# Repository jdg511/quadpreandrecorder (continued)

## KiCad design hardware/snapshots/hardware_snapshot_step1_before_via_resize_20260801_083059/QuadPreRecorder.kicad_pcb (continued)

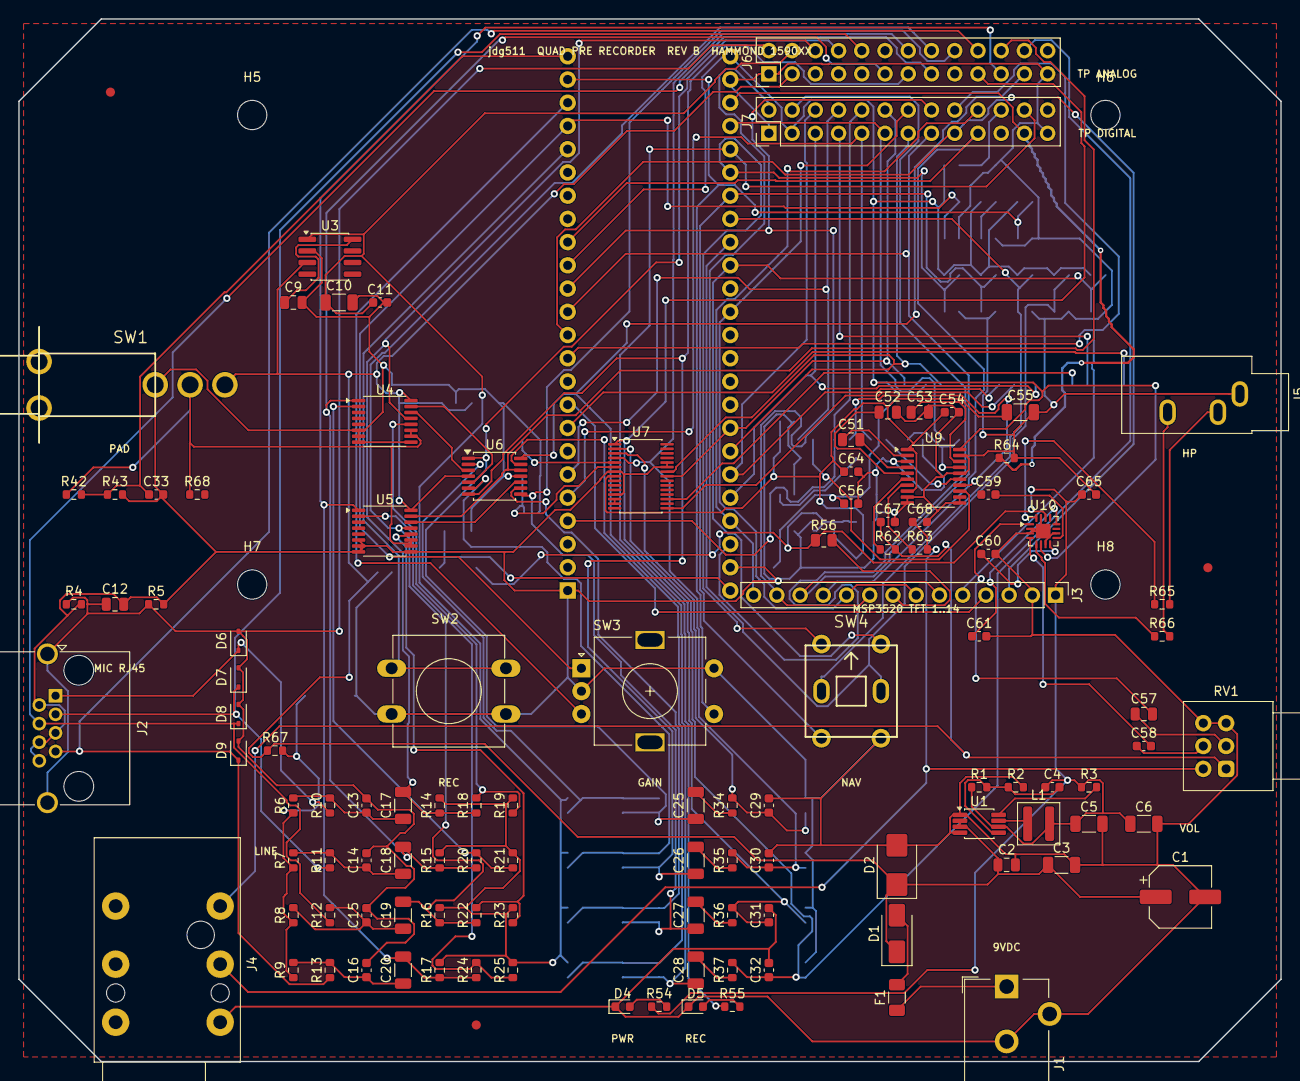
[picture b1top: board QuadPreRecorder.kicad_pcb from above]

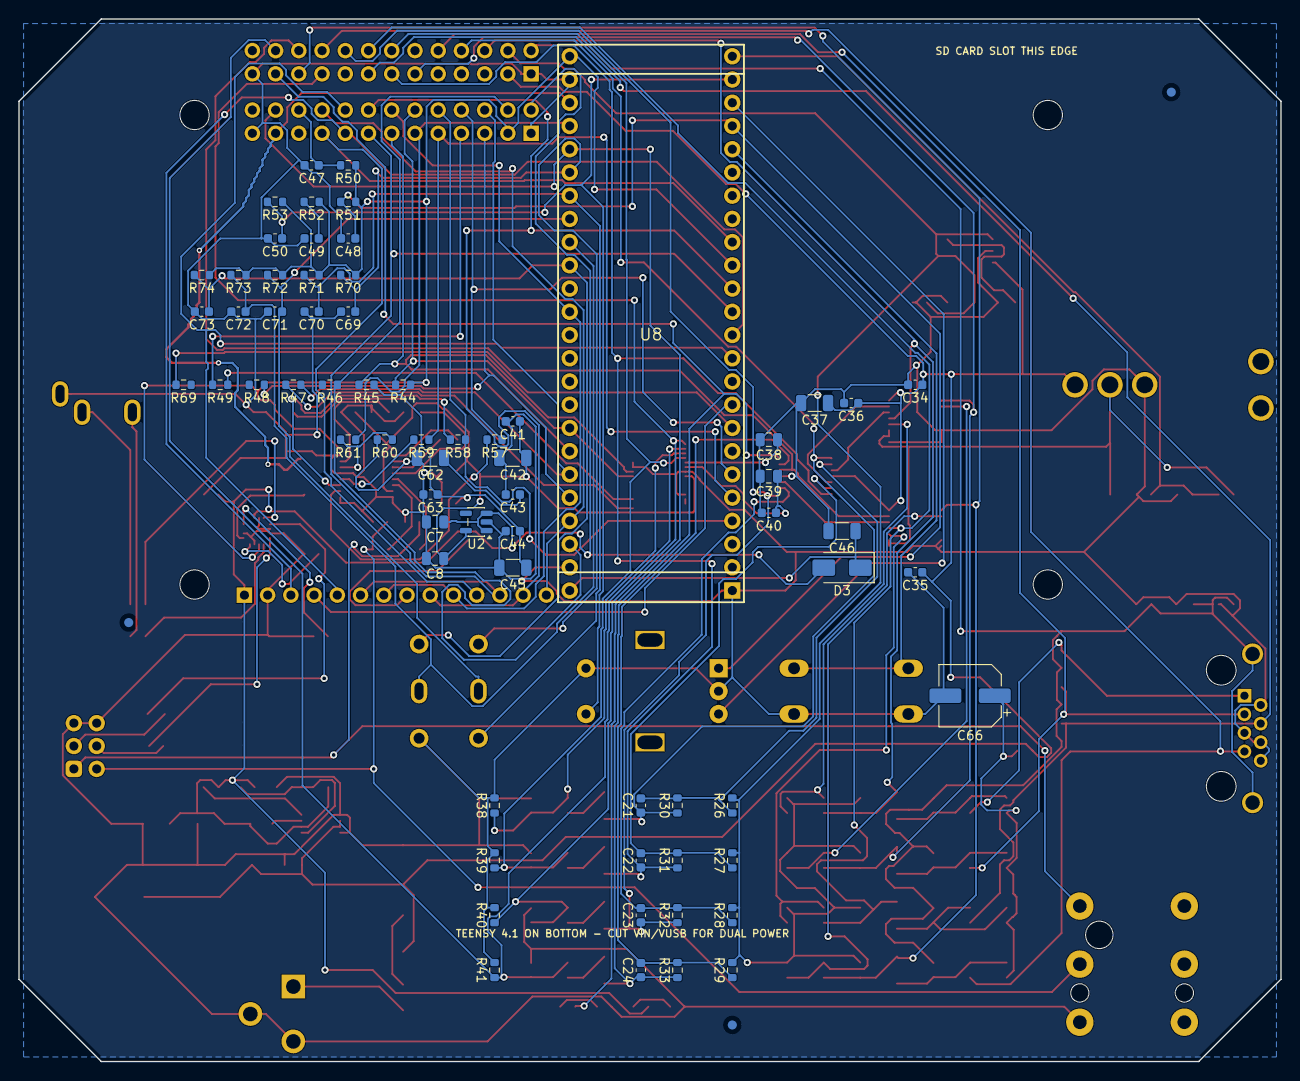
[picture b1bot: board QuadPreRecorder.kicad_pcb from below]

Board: 2 copper layers, 138.0 x 114.0 mm, 190 parts (70 on the bottom side), 119 nets.

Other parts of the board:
FID1, FID2, FID3, FID4, FID5, FID6: Fiducial 1mm; Fiducial_1mm_Mask2mm
H5, H6, H7, H8: M3 TFT MSP3520 PROVISIONAL-VERIFY; MountingHole_3.2mm_M3

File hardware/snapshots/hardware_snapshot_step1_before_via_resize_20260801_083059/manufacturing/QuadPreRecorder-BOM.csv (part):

"Designator","Comment","Footprint","Manufacturer","Manufacturer Part Number","Datasheet","Quantity","DNP"
"C1","100uF 25V","Capacitor_SMD:CP_Elec_6.3x5.8","Panasonic","EEE-FK series low-ESR aluminium electrolytic","","1",""
"C2","100nF 25V","Capacitor_SMD:C_0805_2012Metric","Murata","GRM series X7R/C0G","","1",""
"C3","10uF 25V","Capacitor_SMD:C_1206_3216Metric","Murata","GRM series X7R/C0G","","1",""
"C4,C21-C24","22pF C0G","Capacitor_SMD:C_0603_1608Metric","Murata","GRM series X7R/C0G","","5",""
"C5,C6","22uF 10V","Capacitor_SMD:C_1206_3216Metric","Murata","GRM series X7R/C0G","","2",""
"C7,C9","1uF 10V","Capacitor_SMD:C_0805_2012Metric","Murata","GRM series X7R/C0G","","2",""
"C8","4.7uF 10V","Capacitor_SMD:C_0805_2012Metric","Murata","GRM series X7R/C0G","","1",""
"C10","47uF 10V","Capacitor_SMD:C_1206_3216Metric","Murata","GRM series X7R/C0G","","1",""
"C11,C33-C36,C40,C41,C43,C44,C47,C50,C54,C56,C63,C64,C69-C73","100nF","Capacitor_SMD:C_0603_1608Metric","Murata","GRM series X7R/C0G","","20",""
"C12","1nF 1kV C0G","Capacitor_SMD:C_0805_2012Metric","Murata","GRM series X7R/C0G","","1",""
"C13-C16","100pF C0G","Capacitor_SMD:C_0603_1608Metric","Murata","GRM series X7R/C0G","","4",""
"C17-C20,C25-C28","4.7uF 16V","Capacitor_SMD:C_1206_3216Metric","Murata","GRM series X7R/C0G","","8",""
"C29-C32","10nF C0G","Capacitor_SMD:C_0603_1608Metric","Murata","GRM series X7R/C0G","","4",""
"C37","10uF 16V","Capacitor_SMD:C_1206_3216Metric","Murata","GRM series X7R/C0G","","1",""
"C38,C39,C53","1uF","Capacitor_SMD:C_0805_2012Metric","Murata","GRM series X7R/C0G","","3",""
"C42,C45,C46,C55,C62","10uF","Capacitor_SMD:C_1206_3216Metric","Murata","GRM series X7R/C0G","","5",""
"C48,C49","10nF","Capacitor_SMD:C_0603_1608Metric","Murata","GRM series X7R/C0G","","2",""
"C51,C52","2.2uF","Capacitor_SMD:C_0805_2012Metric","Murata","GRM series X7R/C0G","","2",""
"C57","680nF X7R","Capacitor_SMD:C_0805_2012Metric","Murata","GRM series X7R/C0G","","1",""
"C58","680nF X7R","Capacitor_SMD:C_0603_1608Metric","Murata","GRM series X7R/C0G","","1",""
"C59","1uF","Capacitor_SMD:C_0603_1608Metric","Murata","GRM series X7R/C0G","","1",""
"C60,C61,C65","2.2uF","Capacitor_SMD:C_0603_1608Metric","Murata","GRM series X7R/C0G","","3",""
"C66","100uF 16V","Capacitor_SMD:CP_Elec_6.3x5.8","Panasonic","EEE-FK series low-ESR aluminium electrolytic","","1",""
"C67,C68","2.2nF C0G","Capacitor_SMD:C_0603_1608Metric","Murata","GRM series X7R/C0G","","2",""
"D1,D3","SS14","Diode_SMD:D_SMA","Diodes Incorporated","SS14-13-F","","2",""
"D2","SMBJ12A","Diode_SMD:D_SMB","Littelfuse","SMBJ12A","","1",""
"D4","POWER BLUE","LED_SMD:LED_0603_1608Metric","Lite-On","LTST-C190TBKT","","1",""
"D5","RECORD RED","LED_SMD:LED_0603_1608Metric","Lite-On","LTST-C190KRKT","","1",""
"D6-D9","PESD12VL1BA","Diode_SMD:D_SOD-323","Nexperia","PESD12VL1BA,115","https://assets.nexperia.com/documents/data-sheet/PESD12VL1BA.pdf","4",""
"F1","750mA PTC","Fuse:Fuse_1206_3216Metric","Littelfuse","1206L075/13.2WR","","1",""
"J1","9V DC IN","Connector_BarrelJack:BarrelJack_CUI_PJ-102AH_Horizontal","CUI Devices","PJ-102AH","","1",""
"J2","AMBISONIC MIC DE-9","Connector_Dsub:DSUB-9_Socket_Horizontal_P2.77x2.84mm_EdgePinOffset9.40mm","Amphenol ICC","LD09S33E4GV00LF","","1",""
"J3","MSP2834 TFT CTP 14PIN HEADER","Connector_PinHeader_2.54mm:PinHeader_1x14_P2.54mm_Vertical","Sullins Connector Solutions","PRPC014SAAN-RC","","1",""
"J4","1/4in BINAURAL LINE OUT","Connector_Audio:Jack_6.35mm_Neutrik_NRJ6HF_Horizontal","Neutrik","NRJ6HF","","1",""
"J5","1/8in BINAURAL HEADPHONE OUT","Connector_Audio:Jack_3.5mm_CUI_SJ1-3533NG_Horizontal","CUI Devices","SJ1-3533NG","","1",""
"J6","ANALOG DEBUG DB-25","Connector_Dsub:DSUB-25_Socket_Horizontal_P2.77x2.84mm_EdgePinOffset9.40mm","Generic","Right-angle DB-25 female/socket, 2.77x2.84mm, 9.40mm edge offset","","1",""
"J7","DIGITAL DEBUG DB-25","Connector_Dsub:DSUB-25_Socket_Horizontal_P2.77x2.84mm_EdgePinOffset9.40mm","Generic","Right-angle DB-25 female/socket, 2.77x2.84mm, 9.40mm edge offset","","1",""
"L1","2.2uH 1.5A","Inductor_SMD:L_Abracon_ASPIAIG-F4020","Abracon","ASPIAIG-F4020-2R2M-T","","1",""
"R1","680k","Resistor_SMD:R_0603_1608Metric","Yageo","RC0603FR series, 1%","","1",""
"R2","130k","Resistor_SMD:R_0603_1608Metric","Yageo","RC0603FR series, 1%","","1",""
"R3,R42,R64","100k","Resistor_SMD:R_0603_1608Metric","Yageo","RC0603FR series, 1%","","3",""
"R4,R14-R17","1M","Resistor_SMD:R_0603_1608Metric","Yageo","RC0603FR series, 1%","","5",""
"R5","0R CHASSIS LINK","Resistor_SMD:R_0603_1608Metric","Yageo","RC0603FR series, 1%","","1","DNP"
"R6-R9","4.7k ELECTRET BIAS","Resistor_SMD:R_0603_1608Metric","Yageo","RC0603FR series, 1%","","4",""
"R10-R13","100R RF","Resistor_SMD:R_0603_1608Metric","Yageo","RC0603FR series, 1%","","4",""
"R18,R20,R22,R24","68k 0.1%","Resistor_SMD:R_0603_1608Metric","Vishay","TNPW0603 series, 0.1%","","4",""
"R19,R21,R23,R25","33k 0.1%","Resistor_SMD:R_0603_1608Metric","Vishay","TNPW0603 series, 0.1%","","4",""
"R26-R29","10k 0.1%","Resistor_SMD:R_0603_1608Metric","Vishay","TNPW0603 series, 0.1%","","4",""
"R30-R33","90.9k 0.1%","Resistor_SMD:R_0603_1608Metric","Vishay","TNPW0603 series, 0.1%","","4",""
"R34-R37,R61","100R","Resistor_SMD:R_0603_1608Metric","Yageo","RC0603FR series, 1%","","5",""
"R38-R41","100k","Resistor_SMD:R_0603_1608Metric","Yageo","RC0603FR series, 1%","","4","DNP"
"R43","47k","Resistor_SMD:R_0603_1608Metric","Yageo","RC0603FR series, 1%","","1",""
"R44,R45","4.7k","Resistor_SMD:R_0603_1608Metric","Yageo","RC0603FR series, 1%","","2",""
"R46-R49,R57-R59,R69","33R","Resistor_SMD:R_0603_1608Metric","Yageo","RC0603FR series, 1%","","8",""
"R50-R53,R60,R70-R74","10k","Resistor_SMD:R_0603_1608Metric","Yageo","RC0603FR series, 1%","","10",""
"R54","2.2k","Resistor_SMD:R_0603_1608Metric","Yageo","RC0603FR series, 1%","","1",""
"R55,R68","1k","Resistor_SMD:R_0603_1608Metric","Yageo","RC0603FR series, 1%","","2",""
"R56","100R TFT BACKLIGHT","Resistor_SMD:R_0805_2012Metric","Yageo","RC0805FR-07100RL","","1",""
"R62,R63","470R","Resistor_SMD:R_0603_1608Metric","Yageo","RC0603FR series, 1%","","2",""
"R65,R66","10R","Resistor_SMD:R_0603_1608Metric","Yageo","RC0603FR series, 1%","","2",""
"R67","100R MIC BIAS FILTER","Resistor_SMD:R_0603_1608Metric","Yageo","RC0603FR series, 1%","","1",""
"RV1","10kA HEADPHONE VOLUME","QuadPreRecorder:RK097_Dual_Horizontal_NoEdgeGuide","Alps Alpine","RK0971221-F15-C0-A103","","1",""
"SW1","PAD -10dB","QuadPreRecorder:SW_Toggle_ESwitch_100SP_M7","E-Switch","100SP1T1B1M7REH","","1",""
"SW2","RECORD START/STOP","Button_Switch_THT:SW_PUSH-12mm","Omron","B3F-5150","","1",""
"SW3","MASTER GAIN","Rotary_Encoder:RotaryEncoder_Alps_EC11E-Switch_Vertical_H20mm","Alps Alpine","EC11E15244G1","","1",""
"SW4","TFT MENU NAV","QuadPreRecorder:SW_Nav_ALPS_SKQUCAA010","Alps Alpine","SKQUCAA010","https://cdn-shop.adafruit.com/datasheets/SKQUCAA010-ALPS.pdf","1",""
"U1","TPS62160DGK","Package_SO:VSSOP-8_3x3mm_P0.65mm","Texas Instruments","TPS62160DGKR","https://www.ti.com/lit/ds/symlink/tps62160.pdf","1",""
"U2","TPS7A2033PDBV","Package_TO_SOT_SMD:SOT-23-5","Texas Instruments","TPS7A2033PDBVR","https://www.ti.com/lit/ds/symlink/tps7a20.pdf","1",""
"U3","TLE2426ID","Package_SO:SOIC-8_3.9x4.9mm_P1.27mm","Texas Instruments","TLE2426IDR","https://www.ti.com/lit/ds/symlink/tle2426.pdf","1",""
"U4,U5","CD4053BPW","Package_SO:TSSOP-16_4.4x5mm_P0.65mm","Texas Instruments","CD4053BPWR","https://www.ti.com/lit/ds/symlink/cd4053b.pdf","2",""
"U6","OPA1654","Package_SO:TSSOP-14_4.4x5mm_P0.65mm","Texas Instruments","OPA1654AIPWR","https://www.ti.com/lit/ds/symlink/opa1654.pdf","1",""
"U7","PCM1864DBT","Package_SO:TSSOP-30_4.4x7.8mm_P0.5mm","Texas Instruments","PCM1864DBTR","https://www.ti.com/lit/ds/symlink/pcm1864.pdf","1",""
"U8","Teensy 4.1","QuadPreRecorder:Teensy41_Socket","PJRC","TEENSY41","https://www.pjrc.com/store/teensy41.html","1",""
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
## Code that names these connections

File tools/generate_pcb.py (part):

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        # via, C39 (1u) sits right behind it. (C38, the MICBIAS cap, was
        # deleted: pin 5 is left unconnected per the datasheet.)
        "C39": (83.0, 45.9, 0.0, True),    # 1u   ADC_VREF bulk
        "C40": (82.8, 47.7, 0.0, True),    # 100n ADC_VREF  pin 6 (y 48.5)
        # Rev C3 2026-09-12 decoupling rework (audio audit check 3: the 100 nF
        # decouplers were 2.4-11.7 mm from their pins). U7's supply pins are
        # all on its WEST column at x=80.64 (pins 8 AVDD, 11 LDO, 13/14 DVDD),
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        # via -> cap pad, and the cap's GND pad gets its own fanout via.
        # 10 uF bulk caps sit one column east (x=86.6), behind the 100 nF.
        "C41": (82.8, 49.3, 0.0, True),    # 100n  +3V3_A   pin 8  (y 49.5)
        "C43": (82.8, 50.9, 0.0, True),    # 100n  ADC_LDO  pin 11 (y 51.0)
        "C44": (82.8, 52.5, 0.0, True),    # 100n  +3V3_DC  pin 14 (y 52.5), pin 13 joins on top
        "C42": (87.1, 47.4, 0.0, True),    # 10u   +3V3_A
        "C62": (87.1, 49.85, 0.0, True),   # 10u   ADC_LDO
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        "C54": (97.7, 47.08, 180.0, True),   # 100n +3V3_A  pin 1
        "C64": (97.7, 51.62, 180.0, True),   # 100n +3V3_A  pin 8
        "C56": (102.3, 47.08, 0.0, True),    # 100n +3V3_DC pin 20
        "C53": (102.33, 48.65, 0.0, True),   # 1u   DAC_LDO pin 18 (y 48.38)
        "C55": (99.9, 55.0, 0.0, True),      # 10u  +3V3_A bulk, south of the IC
        # Rev C3: series terminators moved north 1.5 mm to make room for the
        # decoupling columns under U7/U9.
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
